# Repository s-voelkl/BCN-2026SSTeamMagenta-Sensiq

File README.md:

# BCN-2026SSTeamMagenta-Sensiq

Sensiq: Serverless IoT Environmental Monitoring

Sensiq is an end-to-end microcontroller-based Internet of Things (IoT) architecture designed to monitor critical indoor environment quality (IEQ) parameters such as temperature, humidity, light intensity, gas concentration, and flame exposure in real time.

By combining inexpensive ESP32 sensor edge devices with a serverless Amazon Web Services (AWS) cloud backend, Sensiq delivers reliable, low-latency live monitoring alongside cost-efficient historical analytics.

**Key Features:**

- **Edge Node:** ESP32-based multi-sensor array transmitting data via TLS-secured MQTT.
- **Serverless Cloud:** AWS backend for data validation, long-term persistence, and REST API exposure.
- **Web Frontend:** React-based dashboard for visualizing live and historical data without vendor lock-in.
- **Alerting:** Threshold-driven email notifications for critical, safety-relevant events.

## Usage

For usage instructions, please refer to the [usage.md file](USAGE.md) in the root directory of this repository.

## License

The source files are licensed under the MIT License; the documentation is licensed under the Creative Commons Attribution 4.0 International License.

## Code Coverage

The hardware code coverage results can be obtained from ``sys-src/sensiq-hardware/test_output.md``.

The AWS code coverage can be splitted into Python lambda handlers and the AWS infrastructure code.
The Python code coverage results can be obtained from ``sys-src/sensiq-aws/coverage/pytest-lambda-coverage.md``; the Typescript code coverage results using Jest can be found in the ``sys-src/sensiq-aws/coverage/jest-aws-coverage`` directory.

Frontend code coverage results can be found in the ``sys-src/sensiq-frontend/coverage`` directory.

## Hardware Unit

Assembled hardware unit with all sensors and components:

Logical architecture of the hardware unit, see [circuit diagram](sys-doc\kicad-hardware-schematic\circuit_diagram_pdf\circuit_diagram_export_light.pdf).

## AWS Cloud Backend

AWS [architecture diagram](sys-doc/techrep/src/architecture_diagram.pdf).

## React Frontend

Example of the React [frontend dashboard](sys-doc/techrep/src/frontend.pdf).

## Alerting System

An example of an email alert triggered by the [alerting system](sys-doc/techrep/src/email-alert.txt).

## Authors and acknowledgment

Authors of this repository are Simon Völkl ([s.voelkl2@oth-aw.de](mailto:s.voelkl2@oth-aw.de)), Johannes Schieder ([j.schieder@oth-aw.de](mailto:j.schieder@oth-aw.de)), Sebastian Rosner ([s.rosner@oth-aw.de](mailto:s.rosner@oth-aw.de)), and Andre Tien Vu ([a.vu@oth-aw.de](mailto:a.vu@oth-aw.de)). We would like to thank our professor Dr.-Ing. Christoph Neumann for his support and guidance throughout the project.

Support available for this project is limited. Please feel free to reach out to us via email.

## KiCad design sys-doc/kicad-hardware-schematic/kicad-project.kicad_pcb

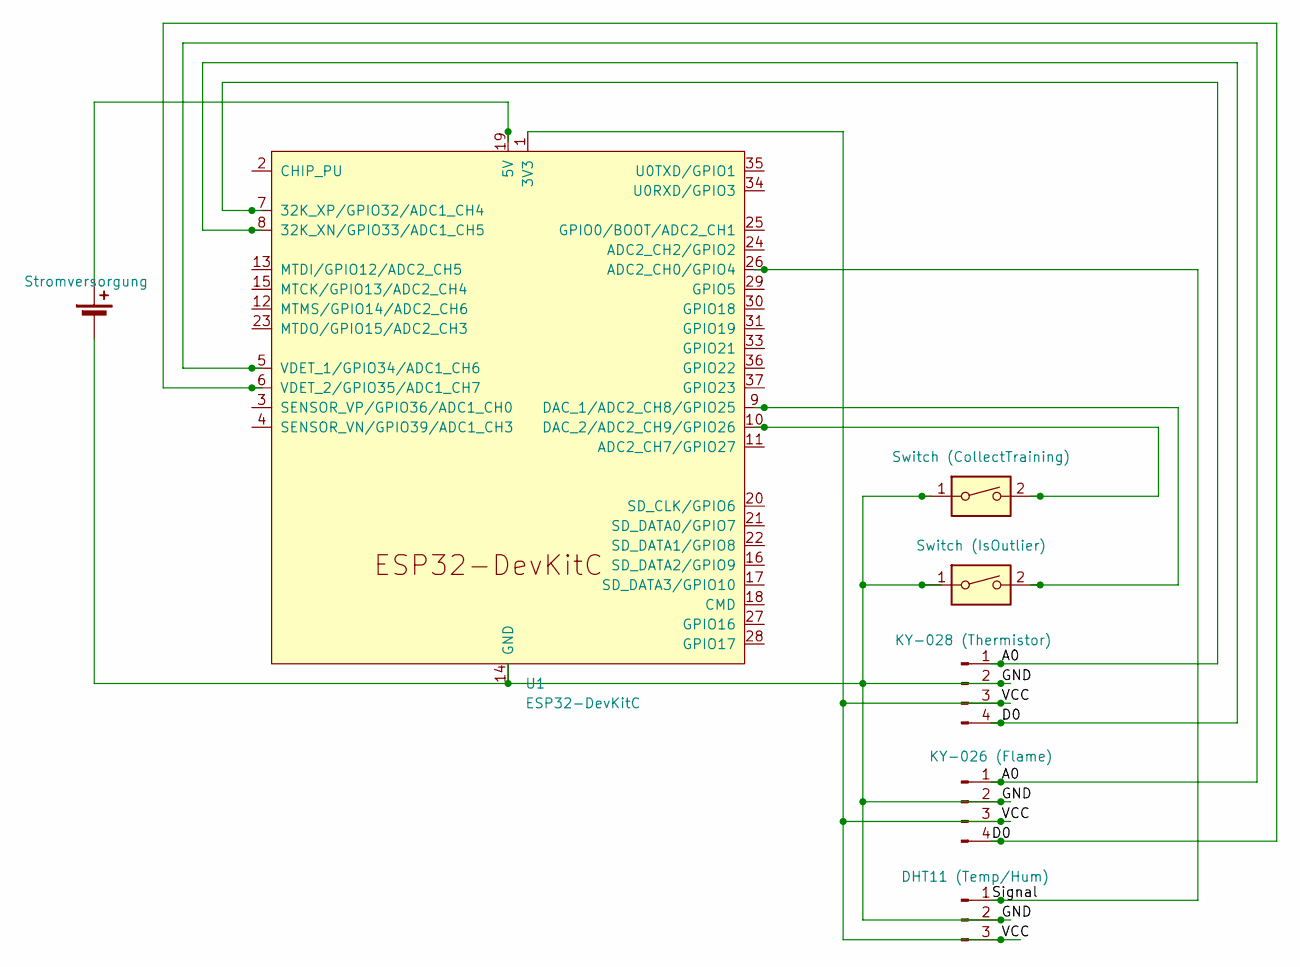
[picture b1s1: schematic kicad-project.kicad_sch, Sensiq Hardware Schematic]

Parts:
BT1: Stromversorgung; TerminalBlock_Phoenix_PT-1,5-2-5.0-H_1x02_P5.00mm_Horizontal
J1: DHT11 (Temp/Hum); PinHeader_1x03_P2.54mm_Vertical
SW1: Switch (CollectTraining); TerminalBlock_Phoenix_PT-1,5-2-5.0-H_1x02_P5.00mm_Horizontal
SW2: Switch (IsOutlier); TerminalBlock_Phoenix_PT-1,5-2-5.0-H_1x02_P5.00mm_Horizontal
U1: ESP32-DevKitC
ky026: KY-026 (Flame); PinHeader_1x04_P2.54mm_Vertical
ky28: KY-028 (Thermistor); PinHeader_1x04_P2.54mm_Vertical

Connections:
/A0: U1.5 (VDET_1/GPIO34/ADC1_CH6), U1.7 (32K_XP/GPIO32/ADC1_CH4), ky026.1, ky28.1
/D0: U1.6 (VDET_2/GPIO35/ADC1_CH7), U1.8 (32K_XN/GPIO33/ADC1_CH5), ky026.4, ky28.4
/GND: BT1.2 (-), J1.2, SW1.1, SW2.1, U1.14 (GND), U1.32 (GND), U1.38 (GND), ky026.2, ky28.2
/Signal: J1.1, U1.26 (ADC2_CH0/GPIO4)
/VCC: J1.3, U1.1 (3V3), ky026.3, ky28.3
unnamed: BT1.1 (+), U1.19 (5V)
unnamed: SW2.2, U1.9 (DAC_1/ADC2_CH8/GPIO25)
unnamed: SW1.2, U1.10 (DAC_2/ADC2_CH9/GPIO26)

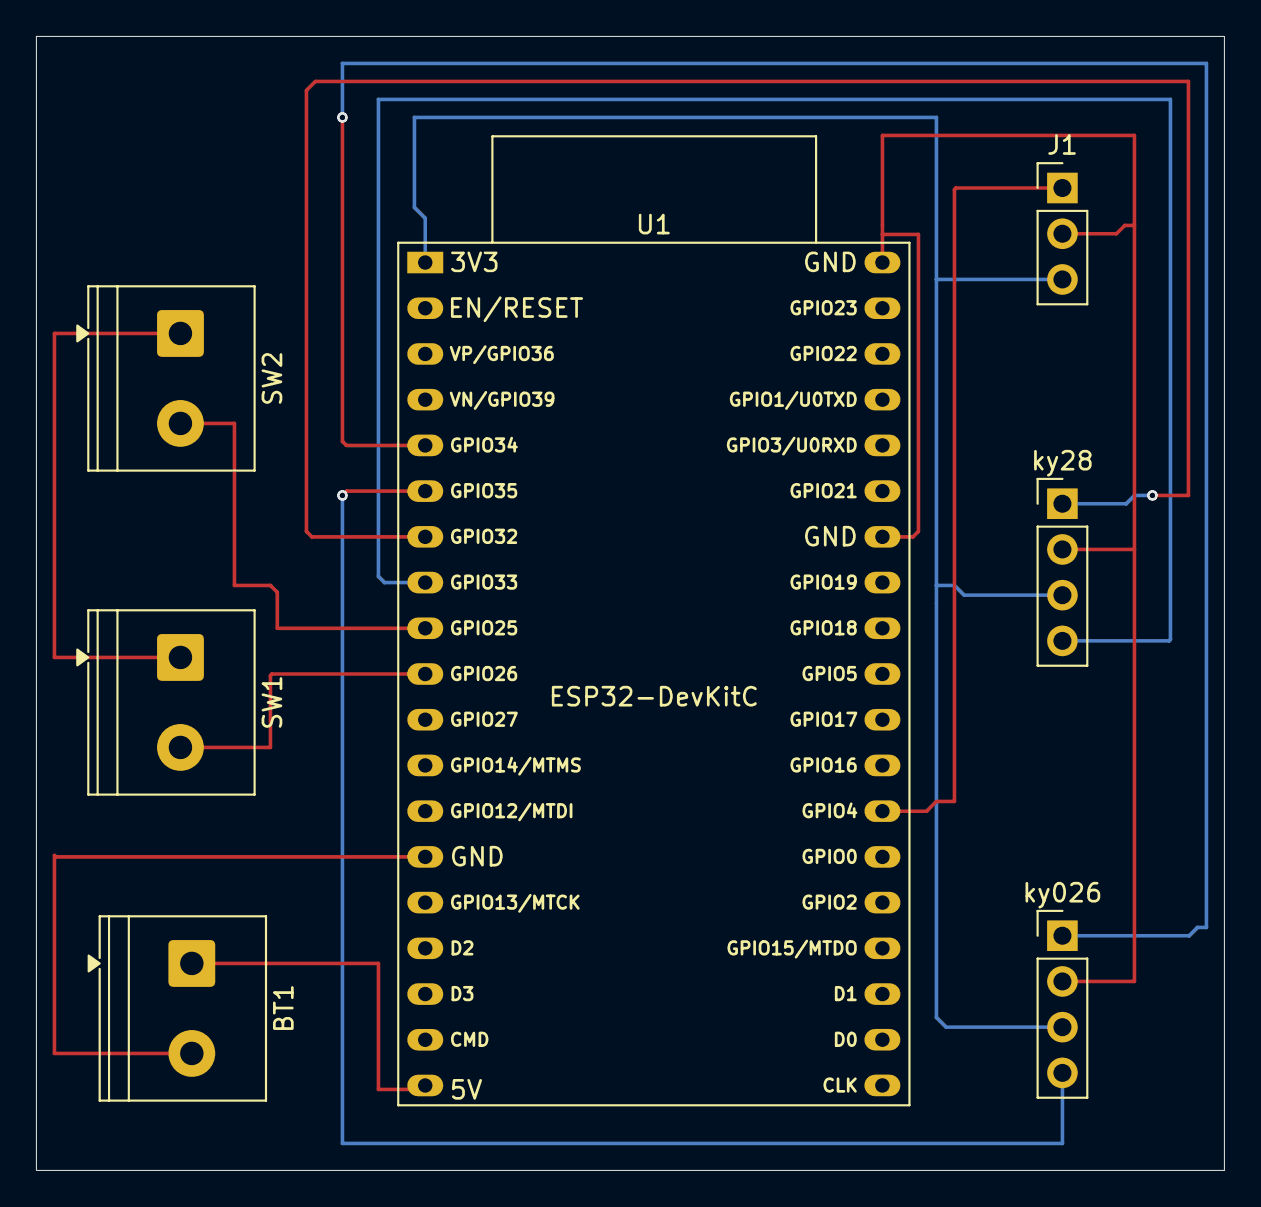
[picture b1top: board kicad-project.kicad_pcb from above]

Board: 2 copper layers, 66.0 x 63.0 mm, 7 parts (0 on the bottom side), 8 nets.

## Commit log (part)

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2026-04-21 initial repository setup
2026-04-24 replaced "filler" with "sensiq"
    this rename here should be fine, due to not having started yet!
    We know, that renaming folders and files is not fine, though only I have edited those files and folders as a setup yet.
2026-05-04 Add Notification Branch to Infra
2026-05-05 LaTeX added technical concept..
    Used listing, cref, itemize, cite.
    Added requirements if needed.
    Updated References.bib
    Update main.tex and references.bib; add technical concept section and enhance references
2026-05-05 Add tech stack, architecture figure, testability
    Move architecture PDF into src and update generated main.pdf. Update main.tex to add a Technology Stack subsection (C++, Python, TypeScript, React), insert a full-width architecture figure (architect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
2026-05-09 Revise concept paper abstract and introduction for clarity; update cost estimation table and add key technical components section
    Revised abstract and keywords.
    Wrote conclusion.
    Wrote key techical components.
    Moved Section Overview.
    Fixed table displays.
    Added crefs for figures and tables.
2026-05-10 Fix overloaded formatting, moved section to designated position, fixed citation problem (somehow)
    Formatting was too overloaded, so simplified it -> less bf text
    Moved related work further down, where it was expected.
    somehow fixed citation problem.
    new problem: author list not shown!
2026-05-11 Add Users
2026-05-13 Rename PDF of concept paper. Rerun latex final time
2026-05-19 Create usage instructions for repo and aws
2026-05-19 Add .gitignore, LICENSE, and notes for MCU sensor setup
2026-05-19 Add template configuration for ESP32 hardware setup
    this is needed for the setup and usage of the arduino file later on.
    it configures credentials and other specificly detailed information.
2026-05-19 Add unit tests for SensorHelper, WifiConnection, and config validation
2026-05-19 Create empty cdk app
2026-05-20 Add instructions to Usage.md
2026-05-20 Rename iot-stack to iot-device-stack
2026-05-24 Add new iot stack
    - This stack is the actual brain of iot core
    - Right now the rules only trigger a cloudwatch log action, which will be replaced by lambda and firehose
    - Also updated dependencies and removed package-lock.json
    - only yarn should be used from now on
2026-05-24 Bump versions in ci pipeline
    + fix linting issues
2026-05-25 Add initial AWS CDK stack and update .gitignore for yarn.lock
2026-05-25 Update AWS CDK stack configuration and adjust example resource imports for clarity
2026-05-25 Refactor SensiqCdkStack: Add demo comments for Lambda function and CloudFormation output resources
2026-05-25 Add basic athena stack
    Add SensiqAthenaStack and corresponding test file for AWS CDK integration. Also add athenaStack to the sensiq.aws.
2026-05-26 Initialize empty history Lambda function with package.json and index.ts
2026-05-26 Refactor MQTT connection handling and update configuration for AWS IoT Core integration
    Switched from MQTT library AsyncMqtt_Generic (Marvin Roger et al.) with TCP and older ESP32 board manager version to the library MQTT by Joel Gaehwiler.
    Updated sensor notes with newer mqtt information.
    updated config.h and template with new AWS thing certificates and no authentification anymore.
    updated mqtt connection for usage of the new mqtt library and support for the three certificates
    fitted existing config test and added simple mqtt connection test
2026-05-26 Move synthTime method to TimeHelper, add Unit Test
2026-05-26 Add unit test output documentation, fix AUnit import problems
    The <AUnit.h> library defines a macro named test(). When this header is included at the top of the file—before system or WiFi library headers—it effectively replaces instances of the word test inside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
    Moved #include <AUnit.h> to the end of the include block in all of the test files (Test_TimeHelper.cpp, Test_MqttConnection.cpp, Test_SensorHelper.cpp, Test_config.cpp, and Test_WifiConnection.cpp).
2026-05-26 Update usage instructions and enhance SensiqIotDeviceStack configuration for AWS IoT integration
    Usage Instructions: Much clearer information on how to use the ESP32 hardware with AWS IoT Core.
    IoT Device Stack:
    - added constant for the "esp32-" name, as name mismatches with the hardware unit appeared.
    - added comments on certificate generation
    - certificates are now inactivated instead of deleted as this lead to deployment problems, though this can be changed back again if really necessary.
    - added receive permission on data topic
2026-05-26 Refactor IAM policy resources in SensiqIotDeviceStack for improved specificity
    Subscribe topics must be accessed with "topicfilter" instead of only "topic".
2026-05-26 Add python lambda setup, enhance athena stack, add lambda functionality
    Enhance AWS IoT and Athena integration:
    - Update .gitignore to exclude VS Code settings.
    - Revise README.md to add AWS IoT Core section.
    - Add Python setup instructions to USAGE.md.
    - Implement handle_history_data Lambda function for querying historical IoT data.
    - Remove obsolete index.py file.
2026-05-28 Redo yarn.lock gitignore commenting in, should not be ignored
    see:
    https://github.com/yarnpkg/yarn/issues/1583
    https://stackoverflow.com/questions/39990017/should-i-commit-the-yarn-lock-file-and-what-is-it-for
2026-05-28 Adjust iot core device tests
2026-05-29 Enhance testing and linting with yarn for both JS and Python, pyproject.toml setup
    Now easy start with yarn test or yarn lint for:
    - lint: eslint for js and ruff for python (with --fix option)
    - test: Jest for js and pytest for python with test coverage console output and writing to file.
    added recommended vscode settings.
2026-05-29 Lint python and ts files, move python test files, update USAGE.md
    Add VS Code configuration for Python testing and linting;
    refactor handle_history_data.py docstrings;
    remove outdated test_handle_history_data.py;
    create new test file for handle_history_data;
    update sensiq-aws.test.ts to disable eslint for require statement
2026-05-29 Enhanc Drawio architecture draft for better explainability
    added names
    added planned AI integration
    moved components
    added background colors
    refined arrows with descriptions
    backup file added to gitignore
2026-05-30 Rename lib to infra
2026-05-30 Move history lambda tests to src/lambda/history
2026-05-30 Add new requirements structure
    This enhances the coldstart speed for each lambda, since not every dependency has to be installed in the runtime
2026-05-30 Change dependencies/ lint configs + pyproject.toml
2026-05-30 Adjust pipeline
2026-05-30 Fix pipelines
2026-05-31 Add validation lambda handler + replace Cloudwatch in IoT Core stack
2026-06-01 Add API Gateway routes for live and history data
2026-06-01 Update BCN Architecture Draft to reflect recent design changes
2026-06-02 Refactor code
    - Split iot core and athena stack into live path and history path
2026-06-02 Enhance comments and format file
2026-06-02 Add test_event.json for history AWS API Gateway request simulation
2026-06-02 Enhance handle_history_data.py with improved query building and logging
    - Introduced partition pruning logic in build_query to optimize Athena queries.
    - Added detailed logging for query execution and error handling.
    - Implemented ISO 8601 date parsing and validation.
    - Updated unit tests to cover new query logic and edge cases.
    - Enhanced comments and docstrings
2026-06-02 Fix cd
2026-06-03 Add draft copy of architecture diagram
2026-06-03 Update .gitignore to include references.bib and modify main.tex basic latex structure
    - Updated .gitignore to exclude references.bib from being ignored.
    - Modified main.tex for a basic setup of the following changes in the sections, added todos
    - tracking references now
2026-06-04 Write introduction section with intro, mission statement, motivation and doc structure
2026-06-04 Frontend setup
    - created a React, vite Typescript frontend with yarn
    - added tailwind, vitest and recharts to dependencies
2026-06-04 Remove vite homepage and add first draft
    - added types for data schema
    - added tanstack api hooks
    - added first 4 components
    - added sample data to display
2026-06-04 Update live mock response format
2026-06-04 Add mock data for history table
2026-06-04 Minor Type fixes
2026-06-04 Prepare and do pdf export of KiCAD project
2026-06-04 rename file
2026-06-04 Add hardware picture for technical report
2026-06-04 Update technical report with extensive hardware, cost and testing and introduction sections
2026-06-04 Set up Docker environment for React.js application with Nginx, update docs
    - Build the Docker image: ``docker build --tag sensiq-frontend-001 .``
    - View Docker images: ``docker images``
    - Run the Docker container: ``docker compose up --build``
    - Optional background run: ``docker compose up --build -d``
    - Show running containers: ``docker ps``
    - Stopping container: ``docker compose down``
2026-06-05 Use history stack lambda in API stack
2026-06-06 Add SNS email alerts for validation lambda
2026-06-07 Update handle_validation.py
    Creating the Lambda Function (handle_validation)
2026-06-07 Create sensiq-live-stack.test.ts
    Adding tests to the live infrastructure
2026-06-07 Add DynamoDB cooldown for SNS alerts
2026-06-08 Added tests for the live lambda sensor, adjusted names, and added new error messages.
2026-06-08 Fix formatting and update links in README.md for clarity
2026-06-08 Shorten too long TEX documentation, add AWS service description and testability for the history route
2026-06-08 Remove TTL
2026-06-08 Minor Design adjustments
2026-06-09 Update sensiq-live-stack.test.ts
    adjustment of spelling
2026-06-09 Remove SNS, adjust the time,
2026-06-09 Cleaned up handle_live_data.py python code
    - Sorted imports
    - Created more constants
    - Added _response() to remove duplication of the five status/header/body dicts.
    - Flattened the nested control flow with many ifs with an early return
    - Docstrings and comments fixed (why decisions happened instead of what happened)
    - Did not change any behaviour (see no test changes), only enhanced code quality
2026-06-09 update tests for 29 second lambda timeout
2026-06-09 Rename athena test to history stack test
2026-06-09 Fix identation, switching to not-deprecated permission granting, add basic docstring
2026-06-10 Add AWS cost estimation
2026-06-10 Time adjustment, unit test adjustment
2026-06-10 Add API key authentication for API Gateway
2026-06-11 Add email warning output, test email subscription, enhance comments
2026-06-11 Refactor alert handling and validation logic; enhance email rendering and update tests for consistency
    - now dynamically asserts value correctness
    - calls rendering python file with a message template
    - add comments and docstrings (!)
    - improve readability and code quality
2026-06-12 Add comments and docstrings
2026-06-12 Fix CloudWatch role
2026-06-12 Rename hardware requirements
2026-06-12 Fix CI for copying the config header file
2026-06-13 Add CORS to history handler
2026-06-13 Install Dependencies for testing; Update .gitignore
2026-06-13 Add basic cn tests
2026-06-13 Replace placeholder hooks with actual api calls
2026-06-13 Add Greeting tests
2026-06-13 Basic tests for Card
2026-06-13 Add tests for SensorChart
2026-06-15 Rename test files
2026-06-15 Update file and library import sources and sort
2026-06-15 Add hardware requirements for Adafruit sensors
2026-06-15 Add CI hardware libraries as requirements
2026-06-15 Integrate TSL2561 sensor readings, tests, libraries and json export
2026-06-15 Cleaning up added sensors
2026-06-15 Update Readme and Usage with newer information for GitHub
2026-06-15 Update sent and validated sensor values
2026-06-15 Fix identation of table
2026-06-15 Update LaTeX to reference original pdf file location
2026-06-15 Change timestamp format in history response
2026-06-15 Add device_id and precision parameter for history handler
    Now requires a device_id to only fetch from relevant devices.
    Additionally adds a aggregation criterium for the precision of the returned data.
2026-06-15 Update Get to Post method of TestEvent
2026-06-15 Add discussion section and update evaluation references in technical report
2026-06-16 Multiple changes
    - added docstrings
    - added loading animation for sensor chart
    - added more KPIs for other sensors
    - adjusted types and schemata
    - implemented lookup table for aggregation interval in backend
    - rewrote tests + added new ones
2026-06-16 Remove old mock data
2026-06-16 Add frontend s3 bucket
2026-06-16 Add vite env vars to cd pipeline
2026-06-16 Add architecture to technical concept section
2026-06-16 Add frontend user interaction
2026-06-16 Add frontend testability section
2026-06-16 Remove unnecessary comment
2026-06-16 Fix identation and spacing
2026-06-17 Fix frontend schema mismatch
2026-06-17 docs: update technical report AWS services section
2026-06-18 add Technical Concept and Summary and Future Work sections
2026-06-18 Update references repo link for later change and TechRep fitting
2026-06-18 Add reference AWS CDK
2026-06-18 Rewrote discussion and future work, fitting summary better
    Discussion is for the "why", future work covers the "what".
2026-06-18 Update drawio architecture
2026-06-18 Rename drawio architecture diagram
2026-06-18 Update newest concept paper pdf file
2026-06-18 Fix cost units and small fixes
2026-06-18 Remove old todos
2026-06-18 Add techrep export file for submission
2026-06-20 fix: live api body and layout
2026-06-20 feat(frontend): visualize sensor thresholds in dashboard
2026-06-21 Remove Line
2026-06-22 Revert "Create git diff"
    This reverts commit 578f6473bdfbc54bb90b5e1609ae76980e5cc0d6.
2026-06-22 change test
2026-06-22 Rename and update TechRep pdf export file
